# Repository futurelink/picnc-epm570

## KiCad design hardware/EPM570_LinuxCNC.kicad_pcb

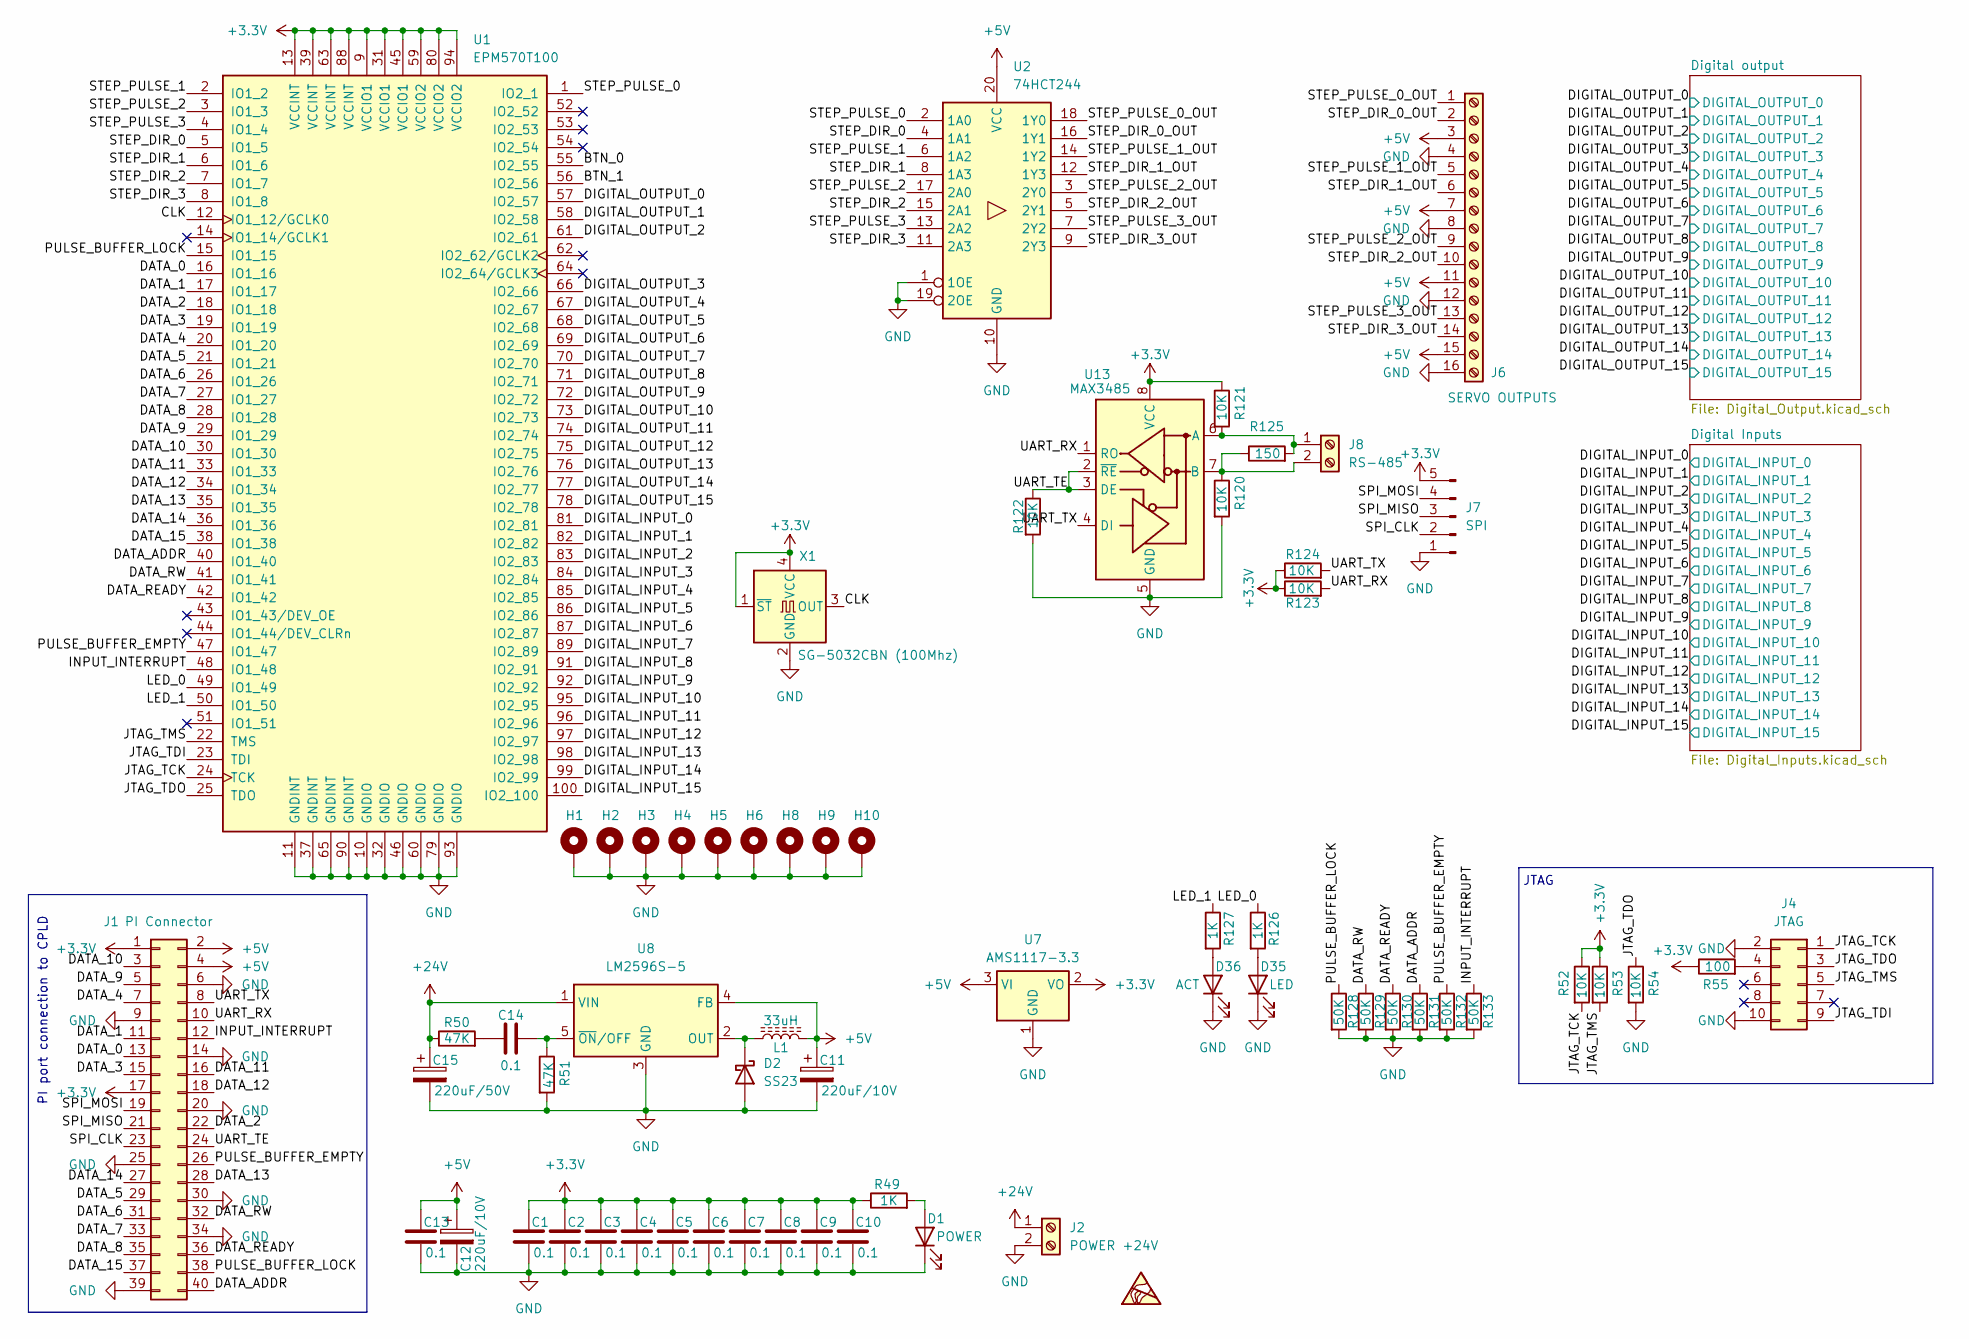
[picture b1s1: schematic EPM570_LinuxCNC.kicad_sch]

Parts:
C1, C2, C3, C4, C5, C6, C7, C8, C9, C10, C13, C14: 0.1; C_0603_1608Metric
C11, C12: 220uF/10V; CP_Elec_6.3x7.7
C15: 220uF/50V; CP_Elec_10x10
D1: POWER; LED_0603_1608Metric
D2: SS23; D_SMA
D35: LED; LED_0603_1608Metric
D36: ACT; LED_0603_1608Metric
H1, H2, H3, H4, H5, H6: MountingHole_Pad; MountingHole_2.7mm_M2.5_ISO7380_Pad
H8, H9, H10: MountingHole_Pad; MountingHole_3.2mm_M3_ISO7380_Pad
J1: PI Connector; PinSocket_2x20_P2.54mm_Vertical
J2: POWER +24V; TerminalBlock_Xinya_XY308-2.54-2P_1x02_P2.54mm_Horizontal
J4: JTAG; IDC-Header_2x05_P2.54mm_Vertical
J6: SERVO OUTPUTS; TerminalBlock_Xinya_XY308-2.54-16P_1x16_P2.54mm_Horizontal
J7: SPI; JST_EH_S5B-EH_1x05_P2.50mm_Horizontal
J8: RS-485; TerminalBlock_Xinya_XY308-2.54-2P_1x02_P2.54mm_Horizontal
L1: 33uH; L_10.4x10.4_H4.8
R49, R126, R127: 1K; R_0603_1608Metric
R50, R51: 47K; R_0603_1608Metric
R52, R53, R54, R120, R121, R122, R123, R124: 10K; R_0603_1608Metric
R55: 100; R_0603_1608Metric
R125: 150; R_0603_1608Metric
R128, R129, R130, R131, R132, R133: 50K; R_0603_1608Metric
U1: EPM570T100; LQFP-100_14x14mm_P0.5mm
U2: 74HCT244; Infineon_PG-DSO-20-32
U7: AMS1117-3.3; SOT-223-3_TabPin2
U8: LM2596S-5; TO-263-5_TabPin3
U13: MAX3485; SOIC-8_3.9x4.9mm_P1.27mm
X1: SG-5032CBN (100Mhz); Oscillator_SMD_SeikoEpson_SG8002LB-4Pin_5.0x3.2mm

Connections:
+3.3V: C1.1, C2.1, C3.1, C4.1, C5.1, C6.1, C7.1, C8.1, C9.1, C10.1, J1.1, J1.17, J7.5, R49.1, R52.1, R53.1, R55.1, R121.1, R123.1, R124.1, U1.9 (VCCIO1), U1.13 (VCCINT), U1.31 (VCCIO1), U1.39 (VCCINT), U1.45 (VCCIO1), U1.59 (VCCIO2), U1.63 (VCCINT), U1.80 (VCCIO2), U1.88 (VCCINT), U1.94 (VCCIO2), U7.2 (VO), U13.8 (VCC), X1.1 (~ST), X1.4 (VCC); also elsewhere on the board
+5V: C11.1, C12.1, C13.1, J1.2, J1.4, J6.3, J6.7, J6.11, J6.15, L1.2, U2.20 (VCC), U7.3 (VI), U8.4 (FB); also elsewhere on the board
+24V: C15.1, J2.1, R50.1, U8.1 (VIN)
/BTN_0: U1.55 (IO2_55)
/BTN_1: U1.56 (IO2_56)
/CLK: U1.12 (IO1_12/GCLK0), X1.3 (OUT)
/DATA_0: J1.13, U1.16 (IO1_16)
/DATA_1: J1.11, U1.17 (IO1_17)
/DATA_2: J1.22, U1.18 (IO1_18)
/DATA_3: J1.15, U1.19 (IO1_19)
/DATA_4: J1.7, U1.20 (IO1_20)
/DATA_5: J1.29, U1.21 (IO1_21)
/DATA_6: J1.31, U1.26 (IO1_26)
/DATA_7: J1.33, U1.27 (IO1_27)
/DATA_8: J1.35, U1.28 (IO1_28)
/DATA_9: J1.5, U1.29 (IO1_29)
/DATA_10: J1.3, U1.30 (IO1_30)
/DATA_11: J1.16, U1.33 (IO1_33)
/DATA_12: J1.18, U1.34 (IO1_34)
/DATA_13: J1.28, U1.35 (IO1_35)
/DATA_14: J1.27, U1.36 (IO1_36)
/DATA_15: J1.37, U1.38 (IO1_38)
/DATA_ADDR: J1.40, R131.1, U1.40 (IO1_40)
/DATA_READY: J1.36, R130.1, U1.42 (IO1_42)
/DATA_RW: J1.32, R129.1, U1.41 (IO1_41)
/DIGITAL_INPUT_0: U1.81 (IO2_81); also elsewhere on the board
/DIGITAL_INPUT_1: U1.82 (IO2_82); also elsewhere on the board
/DIGITAL_INPUT_2: U1.83 (IO2_83); also elsewhere on the board
/DIGITAL_INPUT_3: U1.84 (IO2_84); also elsewhere on the board
/DIGITAL_INPUT_4: U1.85 (IO2_85); also elsewhere on the board
/DIGITAL_INPUT_5: U1.86 (IO2_86); also elsewhere on the board
/DIGITAL_INPUT_6: U1.87 (IO2_87); also elsewhere on the board
/DIGITAL_INPUT_7: U1.89 (IO2_89); also elsewhere on the board
/DIGITAL_INPUT_8: U1.91 (IO2_91); also elsewhere on the board
/DIGITAL_INPUT_9: U1.92 (IO2_92); also elsewhere on the board
/DIGITAL_INPUT_10: U1.95 (IO2_95); also elsewhere on the board
/DIGITAL_INPUT_11: U1.96 (IO2_96); also elsewhere on the board
/DIGITAL_INPUT_12: U1.97 (IO2_97); also elsewhere on the board
/DIGITAL_INPUT_13: U1.98 (IO2_98); also elsewhere on the board
/DIGITAL_INPUT_14: U1.99 (IO2_99); also elsewhere on the board
/DIGITAL_INPUT_15: U1.100 (IO2_100); also elsewhere on the board
/DIGITAL_OUTPUT_0: U1.57 (IO2_57); also elsewhere on the board
/DIGITAL_OUTPUT_1: U1.58 (IO2_58); also elsewhere on the board
/DIGITAL_OUTPUT_2: U1.61 (IO2_61); also elsewhere on the board
/DIGITAL_OUTPUT_3: U1.66 (IO2_66); also elsewhere on the board
/DIGITAL_OUTPUT_4: U1.67 (IO2_67); also elsewhere on the board
/DIGITAL_OUTPUT_5: U1.68 (IO2_68); also elsewhere on the board
/DIGITAL_OUTPUT_6: U1.69 (IO2_69); also elsewhere on the board
/DIGITAL_OUTPUT_7: U1.70 (IO2_70); also elsewhere on the board
/DIGITAL_OUTPUT_8: U1.71 (IO2_71); also elsewhere on the board
/DIGITAL_OUTPUT_9: U1.72 (IO2_72); also elsewhere on the board
/DIGITAL_OUTPUT_10: U1.73 (IO2_73); also elsewhere on the board
/DIGITAL_OUTPUT_11: U1.74 (IO2_74); also elsewhere on the board
/DIGITAL_OUTPUT_12: U1.75 (IO2_75); also elsewhere on the board
/DIGITAL_OUTPUT_13: U1.76 (IO2_76); also elsewhere on the board
/DIGITAL_OUTPUT_14: U1.77 (IO2_77); also elsewhere on the board
/DIGITAL_OUTPUT_15: U1.78 (IO2_78); also elsewhere on the board
/INPUT_INTERRUPT: J1.12, R133.1, U1.48 (IO1_48)
/JTAG_TCK: J4.1, R52.2, U1.24 (TCK)
/JTAG_TDI: J4.9, U1.23 (TDI)
/JTAG_TDO: J4.3, R54.1, U1.25 (TDO)
/JTAG_TMS: J4.5, R53.2, U1.22 (TMS)
/LED_0: R126.1, U1.49 (IO1_49)
/LED_1: R127.1, U1.50 (IO1_50)
/PULSE_BUFFER_EMPTY: J1.26, R132.1, U1.47 (IO1_47)
/PULSE_BUFFER_LOCK: J1.38, R128.1, U1.15 (IO1_15)
/SPI_CLK: J1.23, J7.2
/SPI_MISO: J1.21, J7.3
/SPI_MOSI: J1.19, J7.4
/STEP_DIR_0: U1.5 (IO1_5), U2.4 (1A1)
/STEP_DIR_0_OUT: J6.2, U2.16 (1Y1)
/STEP_DIR_1: U1.6 (IO1_6), U2.8 (1A3)
/STEP_DIR_1_OUT: J6.6, U2.12 (1Y3)
/STEP_DIR_2: U1.7 (IO1_7), U2.15 (2A1)
/STEP_DIR_2_OUT: J6.10, U2.5 (2Y1)
/STEP_DIR_3: U1.8 (IO1_8), U2.11 (2A3)
/STEP_DIR_3_OUT: J6.14, U2.9 (2Y3)
/STEP_PULSE_0: U1.1 (IO2_1), U2.2 (1A0)
/STEP_PULSE_0_OUT: J6.1, U2.18 (1Y0)
/STEP_PULSE_1: U1.2 (IO1_2), U2.6 (1A2)
/STEP_PULSE_1_OUT: J6.5, U2.14 (1Y2)
/STEP_PULSE_2: U1.3 (IO1_3), U2.17 (2A0)
/STEP_PULSE_2_OUT: J6.9, U2.3 (2Y0)
/STEP_PULSE_3: U1.4 (IO1_4), U2.13 (2A2)
/STEP_PULSE_3_OUT: J6.13, U2.7 (2Y2)
/UART_RX: J1.10, R123.2, U13.1 (RO)
/UART_TE: J1.24, R122.1, U13.2 (~RE), U13.3 (DE)
/UART_TX: J1.8, R124.2, U13.4 (DI)
GND: C1.2, C2.2, C3.2, C4.2, C5.2, C6.2, C7.2, C8.2, C9.2, C10.2, C11.2, C12.2, C13.2, C15.2, D1.1 (K), D2.2 (A), D35.1 (K), D36.1 (K), H1.1, H2.1, H3.1, H4.1, H5.1, H6.1, H8.1, H9.1, H10.1, J1.6, J1.9, J1.14, J1.20, J1.25, J1.30, J1.34, J1.39, J2.2, J4.2, J4.10, J6.4, J6.8, J6.12, J6.16, J7.1, R51.2, R54.2, R120.2, R122.2, R128.2, R129.2, R130.2, R131.2, R132.2, R133.2, U1.10 (GNDIO), U1.11 (GNDINT), U1.32 (GNDIO), U1.37 (GNDINT), U1.46 (GNDIO), U1.60 (GNDIO), U1.65 (GNDINT), U1.79 (GNDIO), U1.90 (GNDINT), U1.93 (GNDIO), U2.1 (1OE), U2.10 (GND), U2.19 (2OE), U7.1 (GND), U8.3 (GND), U13.5 (GND), X1.2 (GND); also elsewhere on the board
unnamed: C14.1, R50.2
unnamed: D1.2 (A), R49.2
unnamed: D2.1 (K), L1.1, U8.2 (OUT)
unnamed: D35.2 (A), R126.2
unnamed: D36.2 (A), R127.2
unnamed: J4.4, R55.2
unnamed: J8.1, R121.2, R125.2, U13.6 (A)
unnamed: J8.2, R120.1, R125.1, U13.7 (B)
unnamed: C14.2, R51.1, U8.5 (~ON/OFF)

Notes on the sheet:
PI port connection to CPLD
JTAG

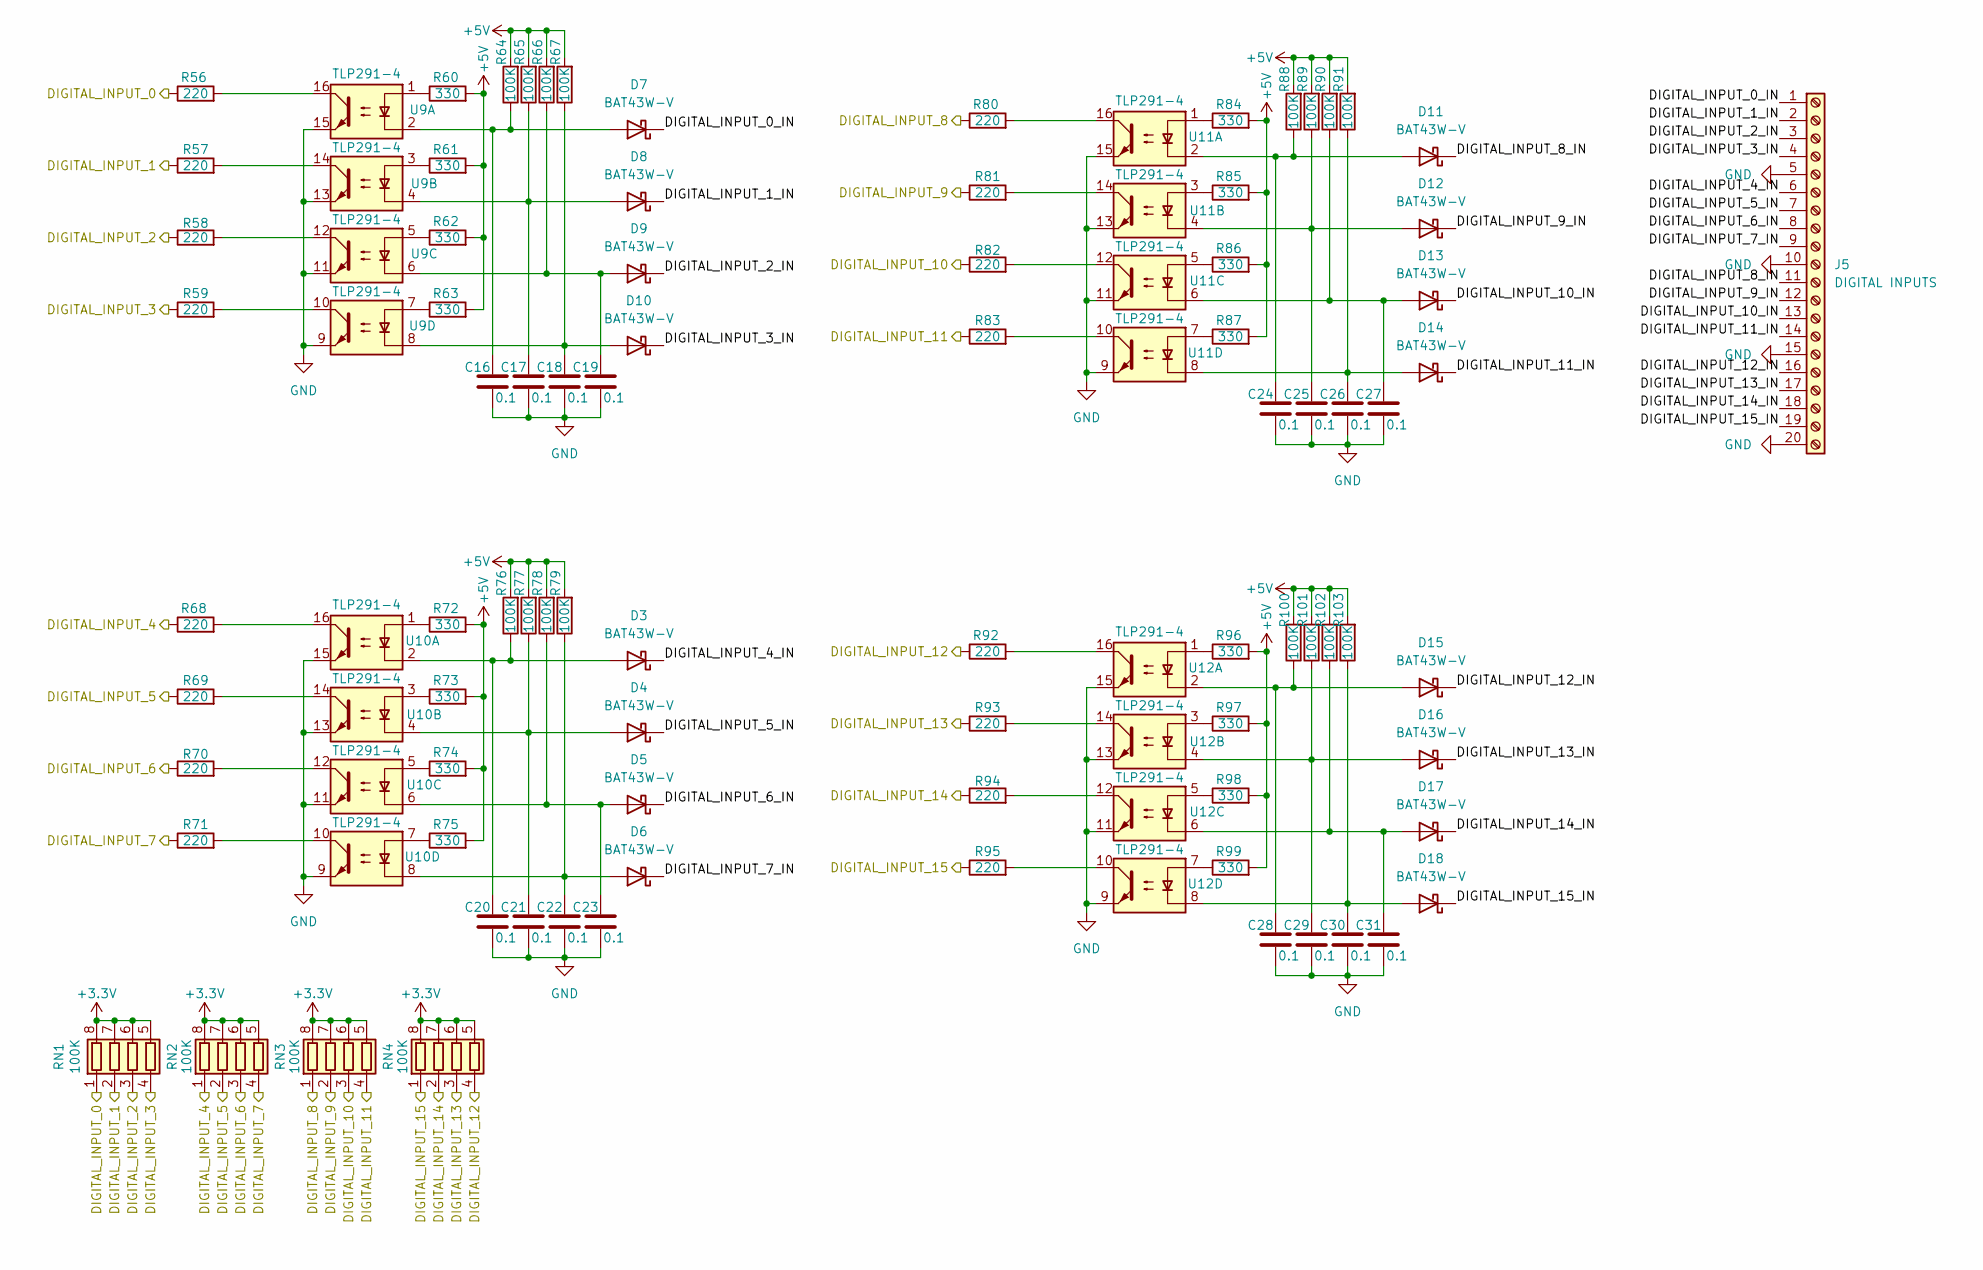
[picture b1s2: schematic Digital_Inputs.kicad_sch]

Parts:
C16, C17, C18, C19, C20, C21, C22, C23, C24, C25, C26, C27, C28, C29, C30, C31: 0.1; C_0603_1608Metric
D3, D4, D5, D6, D7, D8, D9, D10, D11, D12, D13, D14, D15, D16, D17, D18: BAT43W-V; D_SOD-323
J5: DIGITAL INPUTS; TerminalBlock_Xinya_XY308-2.54-20P_1x20_P2.54mm_Horizontal
R56, R57, R58, R59, R68, R69, R70, R71, R80, R81, R82, R83, R92, R93, R94, R95: 220; R_0603_1608Metric
R60, R61, R62, R63, R72, R73, R74, R75, R84, R85, R86, R87, R96, R97, R98, R99: 330; R_0603_1608Metric
R64, R65, R66, R67, R76, R77, R78, R79, R88, R89, R90, R91, R100, R101, R102, R103: 100K; R_0603_1608Metric
RN1, RN2, RN3, RN4: 100K; R_Array_Convex_4x0603
U9, U10, U11, U12: TLP291-4; SOIC-16_4.55x10.3mm_P1.27mm

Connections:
+3.3V: RN1.5 (R4.2), RN1.6 (R3.2), RN1.7 (R2.2), RN1.8 (R1.2), RN2.5 (R4.2), RN2.6 (R3.2), RN2.7 (R2.2), RN2.8 (R1.2), RN3.5 (R4.2), RN3.6 (R3.2), RN3.7 (R2.2), RN3.8 (R1.2), RN4.5 (R4.2), RN4.6 (R3.2), RN4.7 (R2.2), RN4.8 (R1.2); also elsewhere on the board
+5V: R60.2, R61.2, R62.2, R63.2, R64.2, R65.2, R66.2, R67.2, R72.2, R73.2, R74.2, R75.2, R76.2, R77.2, R78.2, R79.2, R84.2, R85.2, R86.2, R87.2, R88.2, R89.2, R90.2, R91.2, R96.2, R97.2, R98.2, R99.2, R100.2, R101.2, R102.2, R103.2; also elsewhere on the board
/DIGITAL_INPUT_0: R56.1, RN1.1 (R1.1); also elsewhere on the board
/DIGITAL_INPUT_1: R57.1, RN1.2 (R2.1); also elsewhere on the board
/DIGITAL_INPUT_2: R58.1, RN1.3 (R3.1); also elsewhere on the board
/DIGITAL_INPUT_3: R59.1, RN1.4 (R4.1); also elsewhere on the board
/DIGITAL_INPUT_4: R68.1, RN2.1 (R1.1); also elsewhere on the board
/DIGITAL_INPUT_5: R69.1, RN2.2 (R2.1); also elsewhere on the board
/DIGITAL_INPUT_6: R70.1, RN2.3 (R3.1); also elsewhere on the board
/DIGITAL_INPUT_7: R71.1, RN2.4 (R4.1); also elsewhere on the board
/DIGITAL_INPUT_8: R80.1, RN3.1 (R1.1); also elsewhere on the board
/DIGITAL_INPUT_9: R81.1, RN3.2 (R2.1); also elsewhere on the board
/DIGITAL_INPUT_10: R82.1, RN3.3 (R3.1); also elsewhere on the board
/DIGITAL_INPUT_11: R83.1, RN3.4 (R4.1); also elsewhere on the board
/DIGITAL_INPUT_12: R92.1, RN4.4 (R4.1); also elsewhere on the board
/DIGITAL_INPUT_13: R93.1, RN4.3 (R3.1); also elsewhere on the board
/DIGITAL_INPUT_14: R94.1, RN4.2 (R2.1); also elsewhere on the board
/DIGITAL_INPUT_15: R95.1, RN4.1 (R1.1); also elsewhere on the board
/Digital Inputs/DIGITAL_INPUT_0_IN: D7.1 (K), J5.1
/Digital Inputs/DIGITAL_INPUT_1_IN: D8.1 (K), J5.2
/Digital Inputs/DIGITAL_INPUT_2_IN: D9.1 (K), J5.3
/Digital Inputs/DIGITAL_INPUT_3_IN: D10.1 (K), J5.4
/Digital Inputs/DIGITAL_INPUT_4_IN: D3.1 (K), J5.6
/Digital Inputs/DIGITAL_INPUT_5_IN: D4.1 (K), J5.7
/Digital Inputs/DIGITAL_INPUT_6_IN: D5.1 (K), J5.8
/Digital Inputs/DIGITAL_INPUT_7_IN: D6.1 (K), J5.9
/Digital Inputs/DIGITAL_INPUT_8_IN: D11.1 (K), J5.11
/Digital Inputs/DIGITAL_INPUT_9_IN: D12.1 (K), J5.12
/Digital Inputs/DIGITAL_INPUT_10_IN: D13.1 (K), J5.13
/Digital Inputs/DIGITAL_INPUT_11_IN: D14.1 (K), J5.14
/Digital Inputs/DIGITAL_INPUT_12_IN: D15.1 (K), J5.16
/Digital Inputs/DIGITAL_INPUT_13_IN: D16.1 (K), J5.17
/Digital Inputs/DIGITAL_INPUT_14_IN: D17.1 (K), J5.18
/Digital Inputs/DIGITAL_INPUT_15_IN: D18.1 (K), J5.19
GND: C16.2, C17.2, C18.2, C19.2, C20.2, C21.2, C22.2, C23.2, C24.2, C25.2, C26.2, C27.2, C28.2, C29.2, C30.2, C31.2, J5.5, J5.10, J5.15, J5.20, U9.9, U9.11, U9.13, U9.15, U10.9, U10.11, U10.13, U10.15, U11.9, U11.11, U11.13, U11.15, U12.9, U12.11, U12.13, U12.15; also elsewhere on the board
unnamed: C20.1, D3.2 (A), R76.1, U10.2
unnamed: C21.1, D4.2 (A), R77.1, U10.4
unnamed: C23.1, D5.2 (A), R78.1, U10.6
unnamed: C22.1, D6.2 (A), R79.1, U10.8
unnamed: C16.1, D7.2 (A), R64.1, U9.2
unnamed: C17.1, D8.2 (A), R65.1, U9.4
unnamed: C19.1, D9.2 (A), R66.1, U9.6
unnamed: C18.1, D10.2 (A), R67.1, U9.8
unnamed: C24.1, D11.2 (A), R88.1, U11.2
unnamed: C25.1, D12.2 (A), R89.1, U11.4
unnamed: C27.1, D13.2 (A), R90.1, U11.6
unnamed: C26.1, D14.2 (A), R91.1, U11.8
unnamed: C28.1, D15.2 (A), R100.1, U12.2
unnamed: C29.1, D16.2 (A), R101.1, U12.4
unnamed: C31.1, D17.2 (A), R102.1, U12.6
unnamed: C30.1, D18.2 (A), R103.1, U12.8
unnamed: R56.2, U9.16
unnamed: R57.2, U9.14
unnamed: R58.2, U9.12
unnamed: R59.2, U9.10
unnamed: R60.1, U9.1
unnamed: R61.1, U9.3
unnamed: R62.1, U9.5
unnamed: R63.1, U9.7
unnamed: R68.2, U10.16
unnamed: R69.2, U10.14
unnamed: R70.2, U10.12
unnamed: R71.2, U10.10
unnamed: R72.1, U10.1
unnamed: R73.1, U10.3
unnamed: R74.1, U10.5
unnamed: R75.1, U10.7
unnamed: R80.2, U11.16
unnamed: R81.2, U11.14
unnamed: R82.2, U11.12
unnamed: R83.2, U11.10
unnamed: R84.1, U11.1
unnamed: R85.1, U11.3
unnamed: R86.1, U11.5
unnamed: R87.1, U11.7
unnamed: R92.2, U12.16
unnamed: R93.2, U12.14
unnamed: R94.2, U12.12
unnamed: R95.2, U12.10
unnamed: R96.1, U12.1
unnamed: R97.1, U12.3
unnamed: R98.1, U12.5
unnamed: R99.1, U12.7

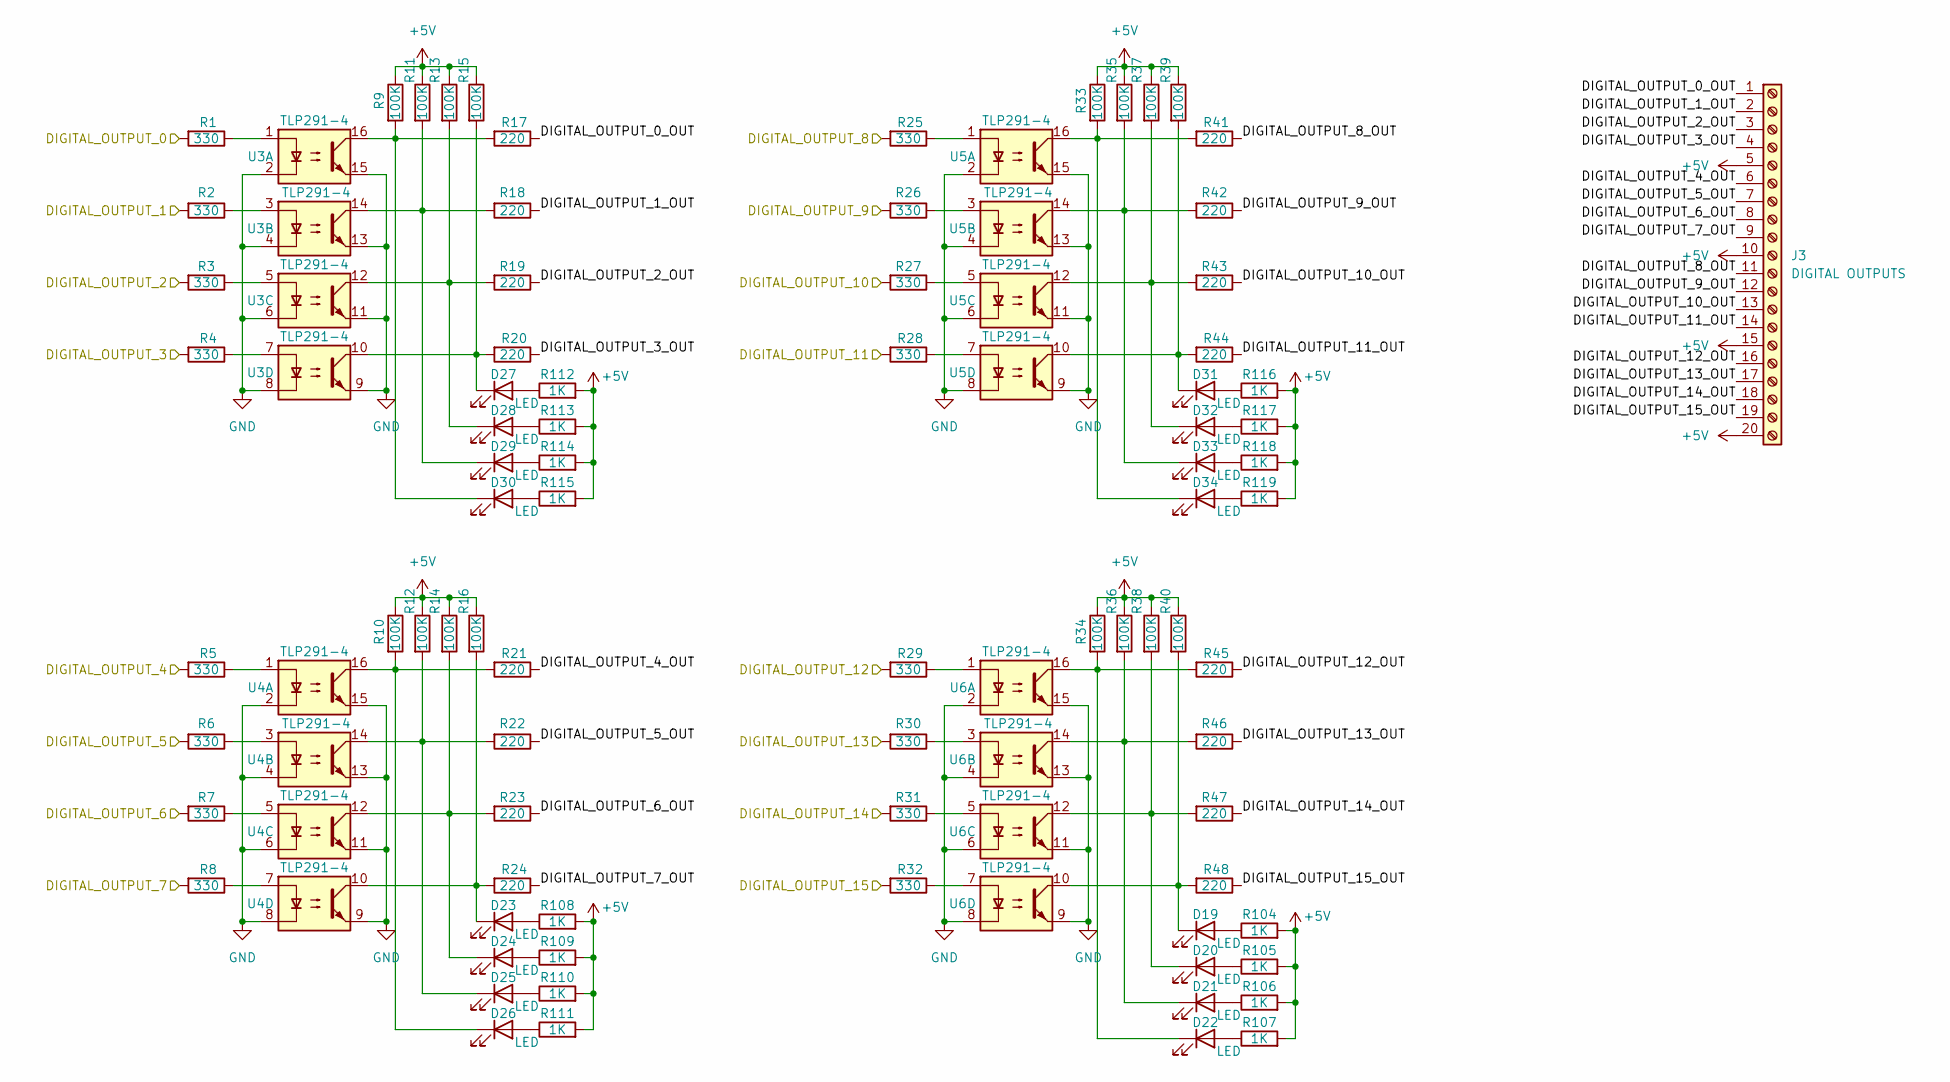
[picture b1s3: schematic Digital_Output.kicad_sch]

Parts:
D19, D20, D21, D22, D23, D24, D25, D26, D27, D28, D29, D30, D31, D32, D33, D34: LED; LED_0603_1608Metric
J3: DIGITAL OUTPUTS; TerminalBlock_Xinya_XY308-2.54-20P_1x20_P2.54mm_Horizontal
R1, R2, R3, R4, R5, R6, R7, R8, R25, R26, R27, R28, R29, R30, R31, R32: 330; R_0603_1608Metric
R9, R10, R11, R12, R13, R14, R15, R16, R33, R34, R35, R36, R37, R38, R39, R40: 100K; R_0603_1608Metric
R17, R18, R19, R20, R21, R22, R23, R24, R41, R42, R43, R44, R45, R46, R47, R48: 220; R_0603_1608Metric
R104, R105, R106, R107, R108, R109, R110, R111, R112, R113, R114, R115, R116, R117, R118, R119: 1K; R_0603_1608Metric
U3, U4, U5, U6: TLP291-4; SOIC-16_4.55x10.3mm_P1.27mm

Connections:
+5V: J3.5, J3.10, J3.15, J3.20, R9.1, R10.1, R11.1, R12.1, R13.1, R14.1, R15.1, R16.1, R33.1, R34.1, R35.1, R36.1, R37.1, R38.1, R39.1, R40.1, R104.2, R105.2, R106.2, R107.2, R108.2, R109.2, R110.2, R111.2, R112.2, R113.2, R114.2, R115.2, R116.2, R117.2, R118.2, R119.2; also elsewhere on the board
/DIGITAL_OUTPUT_0: R1.2; also elsewhere on the board
/DIGITAL_OUTPUT_1: R2.2; also elsewhere on the board
/DIGITAL_OUTPUT_2: R3.2; also elsewhere on the board
/DIGITAL_OUTPUT_3: R4.2; also elsewhere on the board
/DIGITAL_OUTPUT_4: R5.2; also elsewhere on the board
/DIGITAL_OUTPUT_5: R6.2; also elsewhere on the board
/DIGITAL_OUTPUT_6: R7.2; also elsewhere on the board
/DIGITAL_OUTPUT_7: R8.2; also elsewhere on the board
/DIGITAL_OUTPUT_8: R25.2; also elsewhere on the board
/DIGITAL_OUTPUT_9: R26.2; also elsewhere on the board
/DIGITAL_OUTPUT_10: R27.2; also elsewhere on the board
/DIGITAL_OUTPUT_11: R28.2; also elsewhere on the board
/DIGITAL_OUTPUT_12: R29.2; also elsewhere on the board
/DIGITAL_OUTPUT_13: R30.2; also elsewhere on the board
/DIGITAL_OUTPUT_14: R31.2; also elsewhere on the board
/DIGITAL_OUTPUT_15: R32.2; also elsewhere on the board
/Digital output/DIGITAL_OUTPUT_0_OUT: J3.1, R17.1
/Digital output/DIGITAL_OUTPUT_1_OUT: J3.2, R18.1
/Digital output/DIGITAL_OUTPUT_2_OUT: J3.3, R19.1
/Digital output/DIGITAL_OUTPUT_3_OUT: J3.4, R20.1
/Digital output/DIGITAL_OUTPUT_4_OUT: J3.6, R21.1
/Digital output/DIGITAL_OUTPUT_5_OUT: J3.7, R22.1
/Digital output/DIGITAL_OUTPUT_6_OUT: J3.8, R23.1
/Digital output/DIGITAL_OUTPUT_7_OUT: J3.9, R24.1
/Digital output/DIGITAL_OUTPUT_8_OUT: J3.11, R41.1
/Digital output/DIGITAL_OUTPUT_9_OUT: J3.12, R42.1
/Digital output/DIGITAL_OUTPUT_10_OUT: J3.13, R43.1
/Digital output/DIGITAL_OUTPUT_11_OUT: J3.14, R44.1
/Digital output/DIGITAL_OUTPUT_12_OUT: J3.16, R45.1
/Digital output/DIGITAL_OUTPUT_13_OUT: J3.17, R46.1
/Digital output/DIGITAL_OUTPUT_14_OUT: J3.18, R47.1
/Digital output/DIGITAL_OUTPUT_15_OUT: J3.19, R48.1
GND: U3.2, U3.4, U3.6, U3.8, U3.9, U3.11, U3.13, U3.15, U4.2, U4.4, U4.6, U4.8, U4.9, U4.11, U4.13, U4.15, U5.2, U5.4, U5.6, U5.8, U5.9, U5.11, U5.13, U5.15, U6.2, U6.4, U6.6, U6.8, U6.9, U6.11, U6.13, U6.15; also elsewhere on the board
unnamed: D19.2 (A), R104.1
unnamed: D19.1 (K), R40.2, R48.2, U6.10
unnamed: D20.2 (A), R105.1
unnamed: D20.1 (K), R38.2, R47.2, U6.12
unnamed: D21.2 (A), R106.1
unnamed: D21.1 (K), R36.2, R46.2, U6.14
unnamed: D22.2 (A), R107.1
unnamed: D22.1 (K), R34.2, R45.2, U6.16
unnamed: D23.2 (A), R108.1
unnamed: D23.1 (K), R16.2, R24.2, U4.10
unnamed: D24.2 (A), R109.1
unnamed: D24.1 (K), R14.2, R23.2, U4.12
unnamed: D25.2 (A), R110.1
unnamed: D25.1 (K), R12.2, R22.2, U4.14
unnamed: D26.2 (A), R111.1
unnamed: D26.1 (K), R10.2, R21.2, U4.16
unnamed: D27.2 (A), R112.1
unnamed: D27.1 (K), R15.2, R20.2, U3.10
unnamed: D28.2 (A), R113.1
unnamed: D28.1 (K), R13.2, R19.2, U3.12
unnamed: D29.2 (A), R114.1
unnamed: D29.1 (K), R11.2, R18.2, U3.14
unnamed: D30.2 (A), R115.1
unnamed: D30.1 (K), R9.2, R17.2, U3.16
unnamed: D31.2 (A), R116.1
unnamed: D31.1 (K), R39.2, R44.2, U5.10
unnamed: D32.2 (A), R117.1
unnamed: D32.1 (K), R37.2, R43.2, U5.12
unnamed: D33.2 (A), R118.1
unnamed: D33.1 (K), R35.2, R42.2, U5.14
unnamed: D34.2 (A), R119.1
unnamed: D34.1 (K), R33.2, R41.2, U5.16
unnamed: R1.1, U3.1
unnamed: R2.1, U3.3
unnamed: R3.1, U3.5
unnamed: R4.1, U3.7
unnamed: R5.1, U4.1
unnamed: R6.1, U4.3
unnamed: R7.1, U4.5
unnamed: R8.1, U4.7
unnamed: R25.1, U5.1
unnamed: R26.1, U5.3
unnamed: R27.1, U5.5
unnamed: R28.1, U5.7
unnamed: R29.1, U6.1
unnamed: R30.1, U6.3
unnamed: R31.1, U6.5
unnamed: R32.1, U6.7

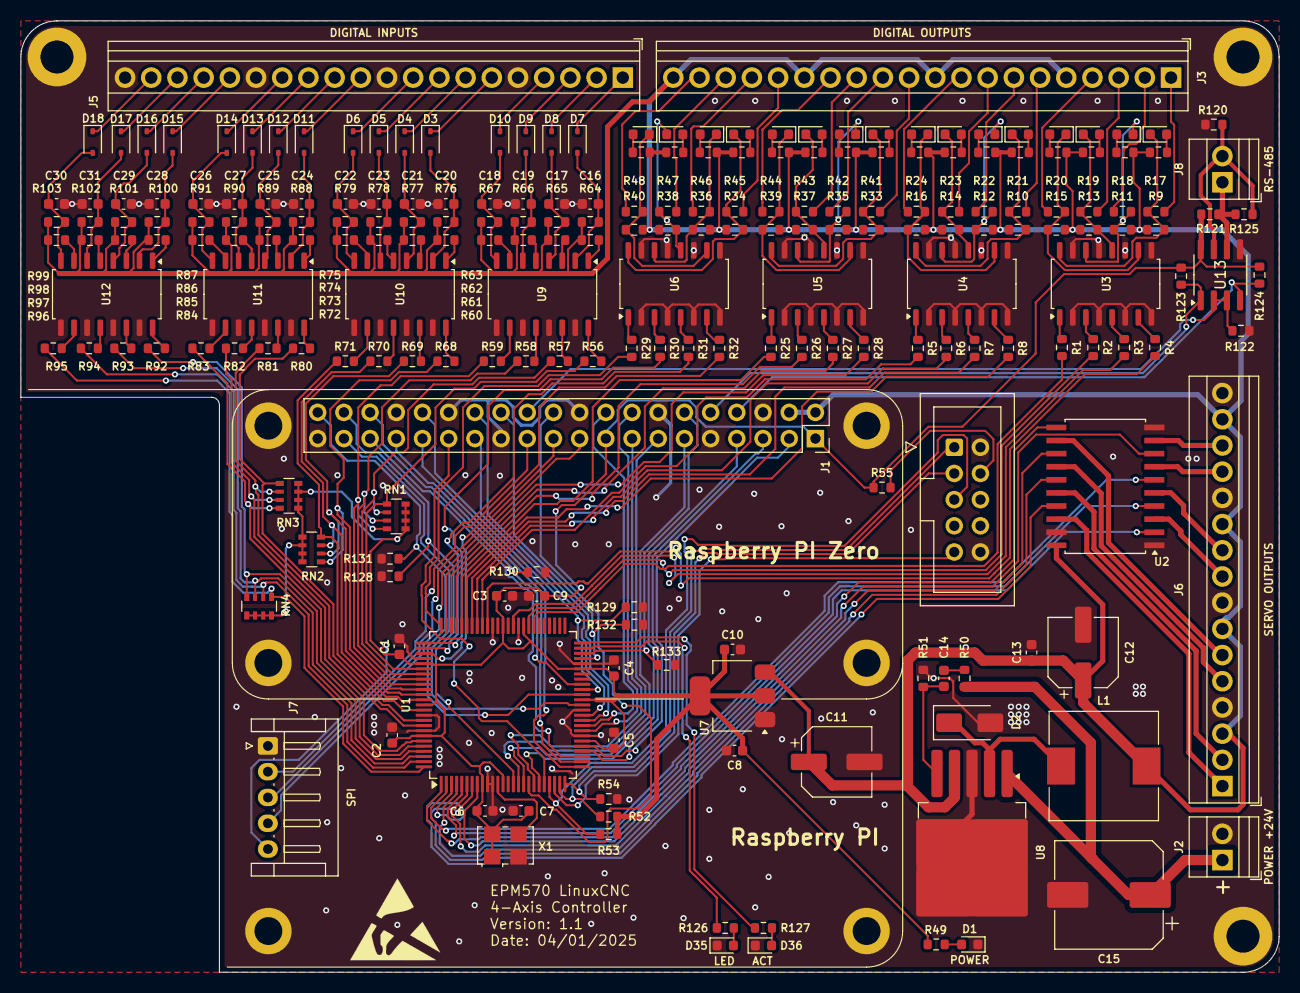
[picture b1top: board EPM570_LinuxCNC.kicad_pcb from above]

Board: 2 copper layers, 122.0 x 92.2 mm, 236 parts (0 on the bottom side), 224 nets.

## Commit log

2025-01-06 PCB fixes. Added pull down resistors.
